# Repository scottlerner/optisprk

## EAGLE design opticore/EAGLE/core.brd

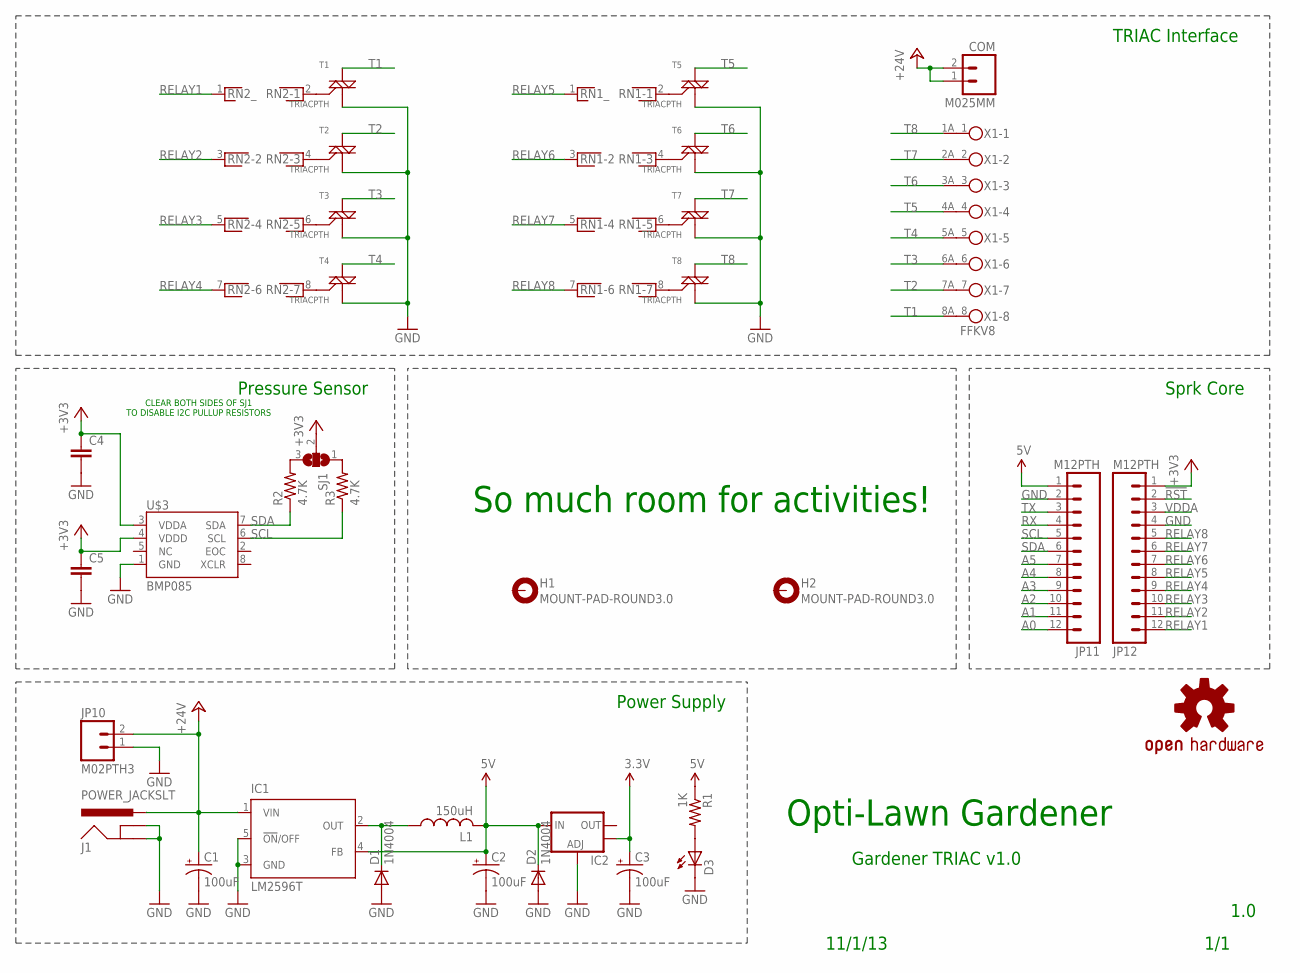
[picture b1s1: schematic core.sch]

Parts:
C1, C2, C3: 100uF; CPOL-RADIAL-100UF-25V; MPN 10NA100MEFC6.3X11
C4, C5: CAP0402-CAP; 0402-CAP
COM: M025MM; SCREWTERMINAL-5MM-2; MPN 724
D1, D2: 1N4004; DO41-10; MPN 1N4004
D3: LED3MM; MPN L-710A8CB/1GD
H1, H2: MOUNT-PAD-ROUND3.0; 3,0-PAD
IC1: LM2596T; T05D; MPN LM2596T-5.0/NOPB
IC2: V_REG_LM1117SOT223; SOT223; MPN LM1117MPX-3.3/NOPB
J1: POWER_JACKSLT; POWER_JACK_SLOT
JP10: M02PTH3; 1X02_LONGPADS
JP11, JP12: M12PTH; 1X12-SMALL-PADS
L1: 150uH; 6000; MPN RLB9012-151KL
LOGO2: OSHW-LOGOL; OSHW-LOGO-L
R1: 1K; AXIAL-0.3; MPN MCF 1W 1K
R2, R3: 4.7K; AXIAL-0.3; MPN MF25 4K7
RN1, RN2: RNX7; RN-8; MPN CSC09A01330RGEK
SJ1: SJ2W; SJ_2
T1, T2, T3, T4, T5, T6, T7, T8: TRIACPTH; TO-92; MPN MAC97A6G
U$3: BMP085
X1: FFKV8

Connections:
3.3V: C3.1 (+), IC2.4 (OUT)
5V: C2.1 (+), D2.C, IC1.4 (FB), IC2.3 (IN), JP11.1, L1.2, R1.P$1 (1)
!RST: JP12.2
+3V3: C4.1, C5.1, JP12.1, SJ1.2, U$3.3 (VDDA), U$3.4 (VDDD)
+24V: C1.1 (+), COM.1, COM.2, IC1.1 (VIN), J1.PWR, JP10.2
A0: JP11.12
A1: JP11.11
A2: JP11.10
A3: JP11.9
A4: JP11.8
A5: JP11.7
GND: C1.2 (-), C2.2 (-), C3.2 (-), C4.2, C5.2, D1.A, D2.A, D3.K (C), IC1.3 (GND), IC1.5 (!ON!/OFF), IC2.1 (ADJ), J1.GND@1 (GNDBREAK), J1.GND@2 (GND), JP10.1, JP11.2, JP12.4, T1.1 (M1), T2.1 (M1), T3.1 (M1), T4.1 (M1), T5.1 (M1), T6.1 (M1), T7.1 (M1), T8.1 (M1), U$3.1 (GND)
unnamed: RN1.4, T6.2 (G)
unnamed: RN1.2, T5.2 (G)
unnamed: RN2.2, T1.2 (G)
unnamed: RN2.4, T2.2 (G)
unnamed: RN2.6, T3.2 (G)
unnamed: RN2.8, T4.2 (G)
unnamed: RN1.6, T7.2 (G)
unnamed: R2.P$2 (2), SJ1.3
unnamed: R3.P$2 (2), SJ1.1
unnamed: D1.C, IC1.2 (OUT), L1.1
unnamed: RN1.8, T8.2 (G)
unnamed: D3.A, R1.P$2 (2)
RELAY1: JP12.12, RN2.1
RELAY2: JP12.11, RN2.3
RELAY3: JP12.10, RN2.5
RELAY4: JP12.9, RN2.7
RELAY5: JP12.8, RN1.1
RELAY6: JP12.7, RN1.3
RELAY7: JP12.6, RN1.5
RELAY8: JP12.5, RN1.7
RX: JP11.4
SCL: JP11.5, R3.P$1 (1), U$3.6 (SCL)
SDA: JP11.6, R2.P$1 (1), U$3.7 (SDA)
T1: T1.3 (M2), X1.8A (2)
T2: T2.3 (M2), X1.7A (2)
T3: T3.3 (M2), X1.6A (2)
T4: T4.3 (M2), X1.5A (2)
T5: T5.3 (M2), X1.4A (2)
T6: T6.3 (M2), X1.3A (2)
T7: T7.3 (M2), X1.2A (2)
T8: T8.3 (M2), X1.1A (2)
TX: JP11.3
VDDA: JP12.3

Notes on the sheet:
TRIAC Interface
Power Supply
Pressure Sensor
CLEAR BOTH SIDES OF SJ1 TO DISABLE I2C PULLUP RESISTORS
Sprk Core
So much room for activities!
Opti-Lawn Gardener
1.0
Gardener TRIAC v1.0
11/1/13
1/1

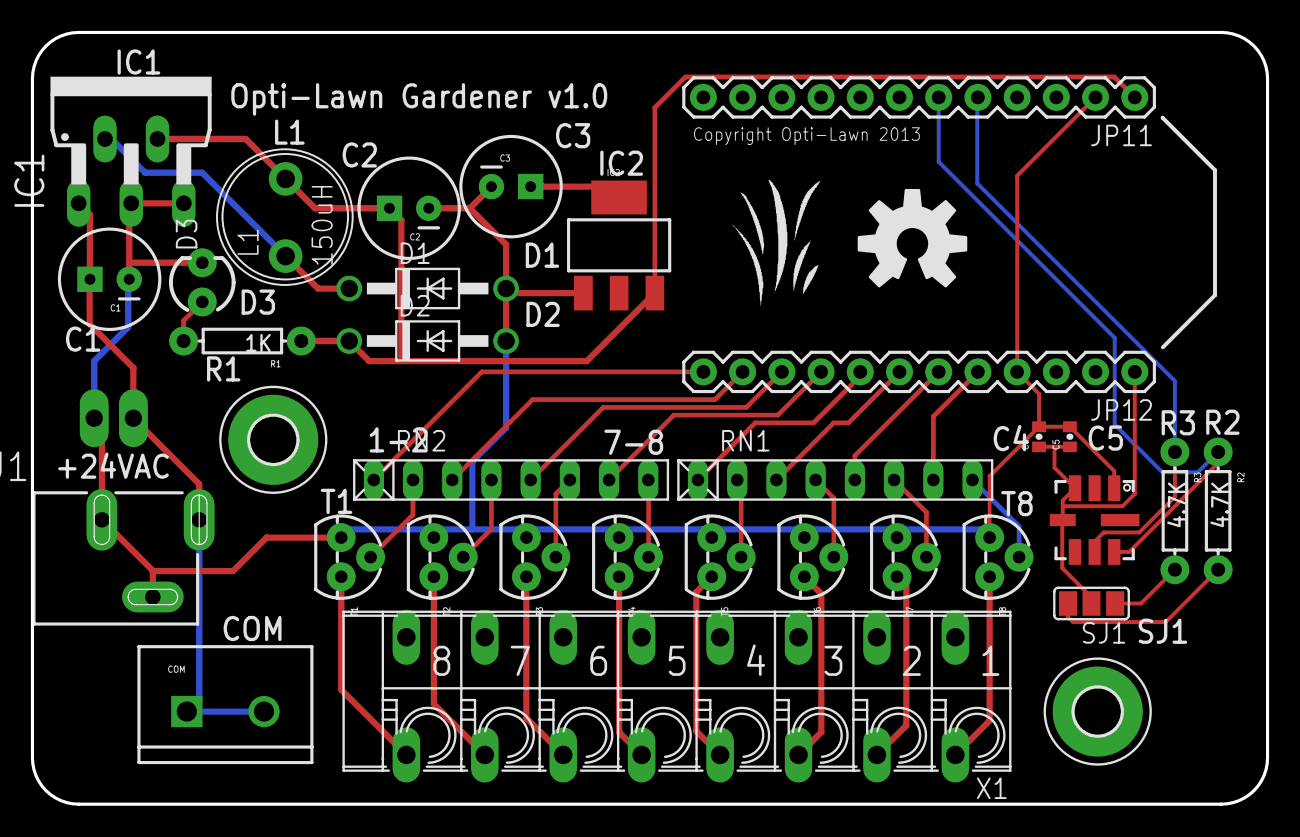
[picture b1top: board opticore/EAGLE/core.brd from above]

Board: 2 copper layers, 80.0 x 50.0 mm, 35 parts (0 on the bottom side), 35 nets.

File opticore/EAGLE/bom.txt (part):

Partlist exported from D:/Users/Scott/Documents/GitHub/optisprk/opticore/EAGLE/core.sch at 11/5/2013 8:52:38 PM

Part  Value              Device             Package               Description                                                                                                                                                                                                        MF MPN              OC_FARNELL OC_NEWARK
C1    100uF              CAP_POLPTH1        CPOL-RADIAL-100UF-25V Capacitor Polarized                                                                                                                                                                                                                                        
C2    100uF              CAP_POLPTH1        CPOL-RADIAL-100UF-25V Capacitor Polarized                                                                                                                                                                                                                                        
C3    100uF              CAP_POLPTH1        CPOL-RADIAL-100UF-25V Capacitor Polarized                                                                                                                                                                                                                                        
C4                       CAP0402-CAP        0402-CAP              Capacitor                                                                                                                                                                                                                                                  
C5                       CAP0402-CAP        0402-CAP              Capacitor                                                                                                                                                                                                                                                  
COM   M025MM             M025MM             SCREWTERMINAL-5MM-2   Standard 2-pin 0.1" header. Use with                                                                                                                                                                                                                       
D1    1N4004             1N4004             DO41-10               DIODE                                                                                                                                                                                                                                                      
D2    1N4004             1N4004             DO41-10               DIODE                                                                                                                                                                                                                                                      
D3                       LED3MM             LED3MM                LEDs                                                                                                                                                                                                                                                       
H1    MOUNT-PAD-ROUND3.0 MOUNT-PAD-ROUND3.0 3,0-PAD               MOUNTING PAD, round                                                                                                                                                                                                                                        
H2    MOUNT-PAD-ROUND3.0 MOUNT-PAD-ROUND3.0 3,0-PAD               MOUNTING PAD, round                                                                                                                                                                                                                                        
IC1   LM2596T            LM2596T            T05D                  SIMPLE SWITCHER® Power Converter 150 kHz 3A Step-Down Voltage Regulator                                                                                                                                               LM2596T-ADJ/LF02 9494162    65K5910  
IC2                      V_REG_LM1117SOT223 SOT223                Voltage Regulator LM1117                                                                                                                                                                                                                                   
J1    POWER_JACKSLT      POWER_JACKSLT      POWER_JACK_SLOT       Power Jack                                                                                                                                                                                                                                                 
JP10  M02PTH3            M02PTH3            1X02_LONGPADS         Standard 2-pin 0.1" header. Use with                                                                                                                                                                                                                       
JP11  M12PTH             M12PTH             1X12-SMALL-PADS       Header 12                                                                                                                                                                                                                                                  
JP12  M12PTH             M12PTH             1X12-SMALL-PADS       Header 12                                                                                                                                                                                                                                                  
L1    150uH              L                  6000                                                                                                                                                                                                                                                                             
LOGO2 OSHW-LOGOL         OSHW-LOGOL         OSHW-LOGO-L           Open Source Hardware Logo This logo indicates the piece of hardware it is found on incorporates a OSHW license and/or adheres to the definition of open source hardware found here: http://freedomdefined.org/OSHW                                         
R1    1K                 RESISTORAXIAL-0.3  AXIAL-0.3             Resistor                                                                                                                                                                                                                                                   
R2    4.7K               RESISTORAXIAL-0.3  AXIAL-0.3             Resistor                                                                                                                                                                                                                                                   
R3    4.7K               RESISTORAXIAL-0.3  AXIAL-0.3             Resistor                                                                                                                                                                                                                                                   
RN1                      RNX7               RN-8                  RESISTOR NETWORK                                                                                                                                                                                                                       unknown    unknown  
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
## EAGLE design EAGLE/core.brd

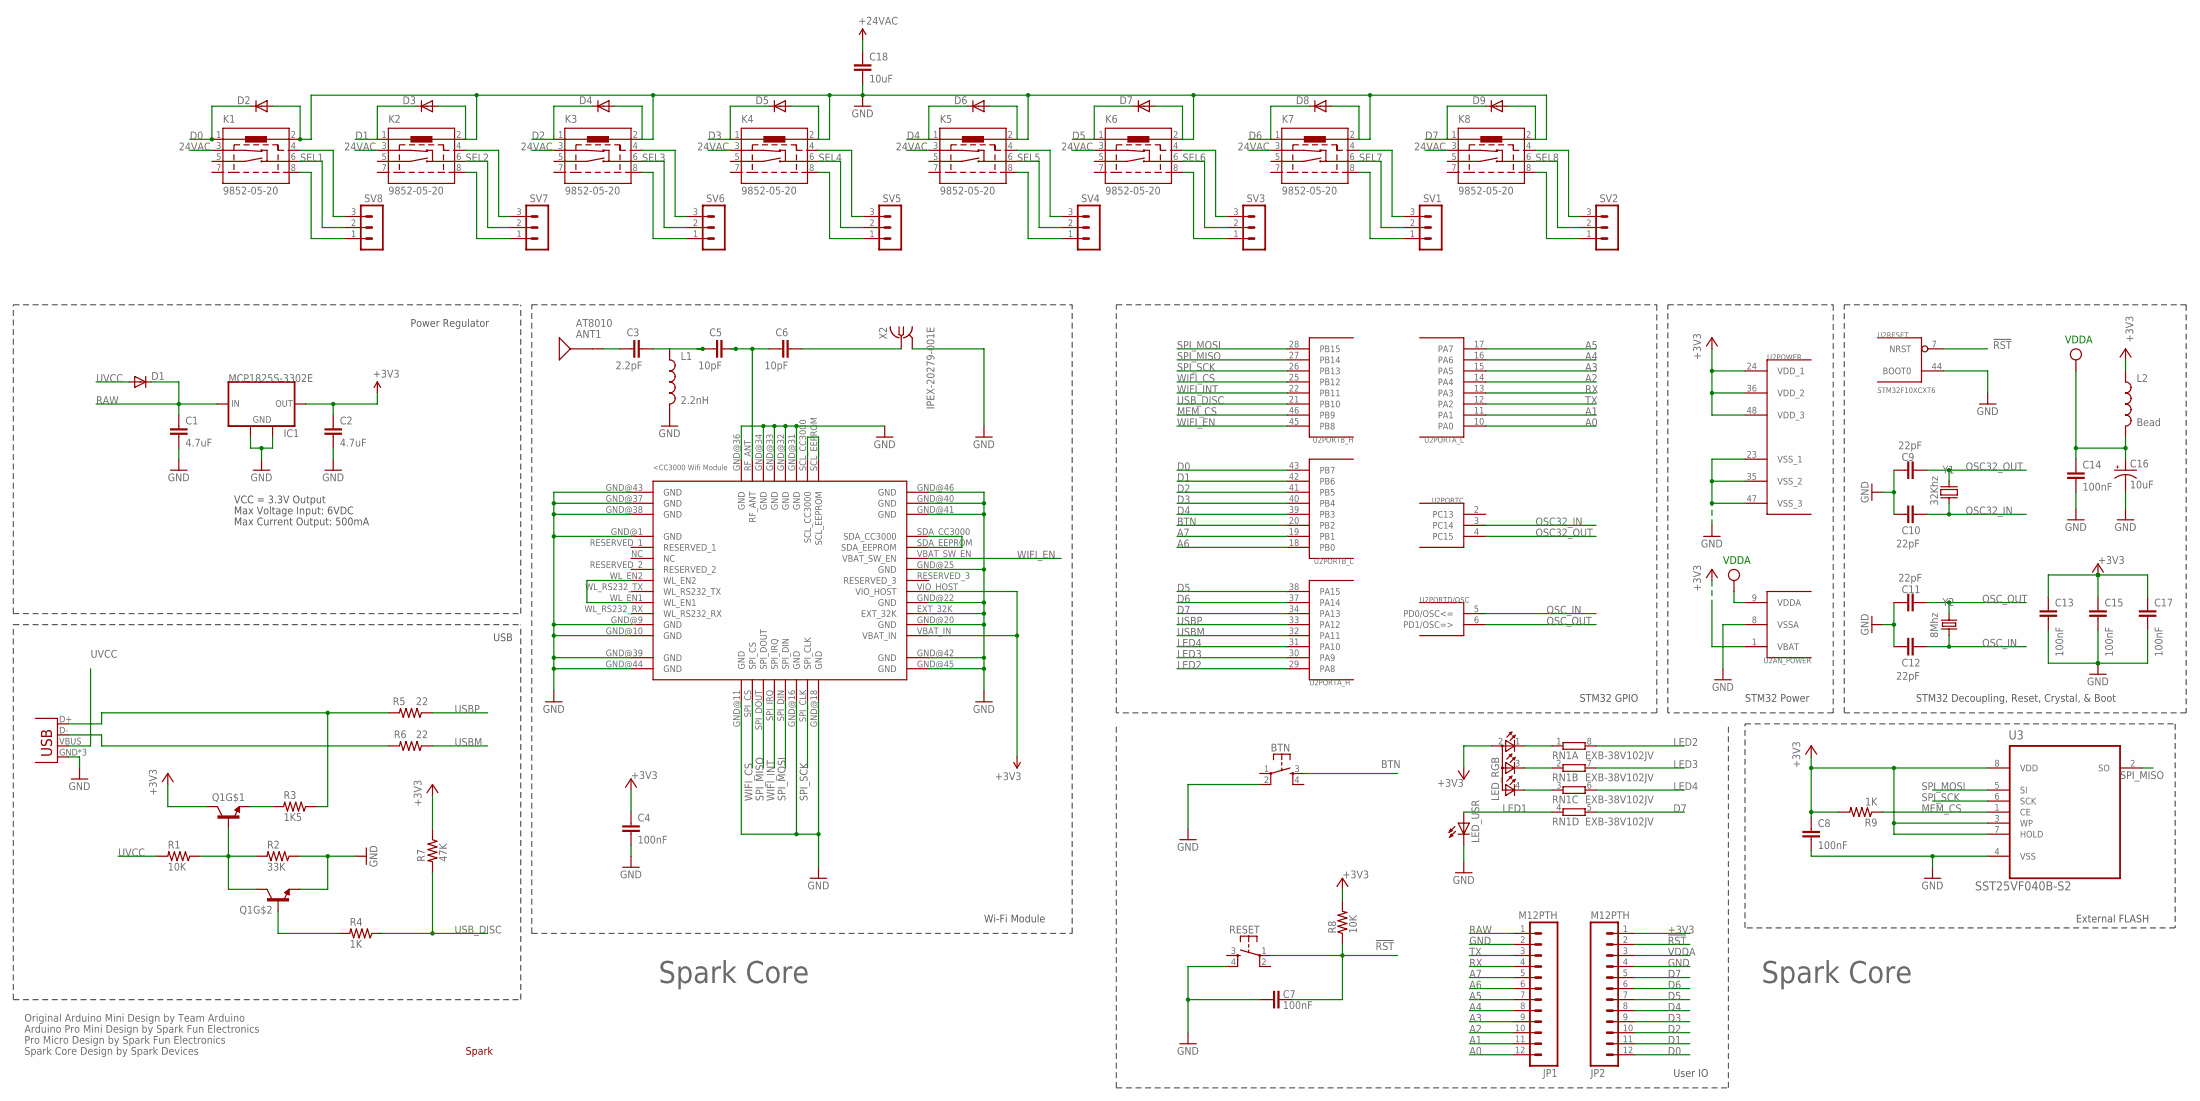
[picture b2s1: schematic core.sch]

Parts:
ANT1: AT8010
BTN: KMR211GLFS; TACTILE_SWITCH_SMD
C1, C2: 4.7uF; C0603
C3: 2.2pF; C0603
C4, C7, C8, C13, C14, C15, C17: 100nF; C0603
C5, C6: 10pF; C0603
C9, C10, C11, C12: 22pF; C0603
C16: 10uF; EIA3216
C18: 10uF; C0603
D1, D2, D3, D4, D5, D6, D7, D8, D9: DIODESOD; SOD-323
IC1: MCP1825S-3302E; SOT223
JP1, JP2: M12PTH; 1X12-SMALL-PADS
K1, K2, K3, K4, K5, K6, K7, K8: 9852-05-20; 9852-20
L1: 2.2nH; 0603
L2: Bead; 0603
LED_RGB: TOPLED-3PLCC; P-LCC-4-3
LED_USR: LED0603; LED-0603
Q1: MMDT3904; SOT363
R1, R8: 10K; R0603
R2: 33K; R0603
R3: 1K5; R0603
R4, R9: 1K; R0603
R5, R6: 22; R0603
R7: 47K; R0603
RESET: KMR211GLFS; TACTILE_SWITCH_SMD
RN1: EXB-38V102JV; EXB38V
SV1, SV2, SV3, SV4, SV5, SV6, SV7, SV8: MA03-1
U1: CC3000
U2: STM32F10XCXT6; TQFP48
U3: SST25VF040B-S2; SOIC127P790X216-8N
U$1: SPARK_LOGO2
X1: USB-MICROB; USB-MICROB-SLOT-HOLE
X2: IPEX-20279-001E
Y1: 32Khz; FC135
Y2: 8Mhz; CRYSTAL-SMD-5X3

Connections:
24VAC: C18.1, K1.3, K2.3, K3.3, K4.3, K5.3, K6.3, K7.3, K8.3
!RST: C7.2, JP2.2, R8.1, RESET.1, U2.7 (NRST)
+3V3: C2.1, C4.1, C8.1, C13.1, C15.1, C17.1, IC1.3 (OUT), JP2.1, L2.1, LED_RGB.2 (A2), Q1.3 (C), R7.1, R8.2, R9.2, U1.VBAT_IN, U1.VIO_HOST, U2.1 (VBAT), U2.24 (VDD_1), U2.36 (VDD_2), U2.48 (VDD_3), U3.3 (WP), U3.7 (HOLD), U3.8 (VDD)
A0: JP1.12, U2.10 (PA0)
A1: JP1.11, U2.11 (PA1)
A2: JP1.10, U2.14 (PA4)
A3: JP1.9, U2.15 (PA5)
A4: JP1.8, U2.16 (PA6)
A5: JP1.7, U2.17 (PA7)
A6: JP1.6, U2.18 (PB0)
A7: JP1.5, U2.19 (PB1)
BTN: BTN.3, U2.20 (PB2)
D0: D2.1 (C), JP2.12, K1.1, U2.43 (PB7)
D1: JP2.11, K2.1, U2.42 (PB6)
D2: JP2.10, K3.1, U2.41 (PB5)
D3: JP2.9, K4.1, U2.40 (PB4)
D4: JP2.8, K5.1, U2.39 (PB3)
D5: JP2.7, K6.1, U2.38 (PA15)
D6: JP2.6, K7.1, U2.37 (PA14)
D7: JP2.5, K8.1, RN1.5 (2), U2.34 (PA13)
D8: D3.1 (C)
D9: D4.1 (C)
D10: D5.1 (C)
D11: D6.1 (C)
D12: D7.1 (C)
D13: D8.1 (C)
D14: D9.1 (C)
GND: BTN.2, C1.2, C2.2, C4.2, C7.1, C8.2, C9.2, C10.2, C11.2, C12.2, C13.2, C14.2, C15.2, C16.C (-), C17.2, C18.2, D2.2 (A), IC1.2 (GND), IC1.4 (GND), JP1.2, JP2.4, K1.2, K2.2, K3.2, K4.2, K5.2, K6.2, K7.2, K8.2, L1.2, LED_USR.C, Q1.1 (E), R2.1, RESET.4, U1.EXT_32K, U1.GND@1 (GND), U1.GND@9 (GND), U1.GND@10 (GND), U1.GND@11 (GND), U1.GND@16 (GND), U1.GND@18 (GND), U1.GND@20 (GND), U1.GND@22 (GND), U1.GND@25 (GND), U1.GND@31 (GND), U1.GND@32 (GND), U1.GND@33 (GND), U1.GND@34 (GND), U1.GND@36 (GND), U1.GND@37 (GND), U1.GND@38 (GND), U1.GND@39 (GND), U1.GND@40 (GND), U1.GND@41 (GND), U1.GND@42 (GND), U1.GND@43 (GND), U1.GND@44 (GND), U1.GND@45 (GND), U1.GND@46 (GND), U2.8 (VSSA), U2.23 (VSS_1), U2.35 (VSS_2), U2.44 (BOOT0), U2.47 (VSS_3), U3.4 (VSS), X1.GND, X1.MT1 (GND), X1.MT2 (GND), X2.2@1 (GND), X2.2@2 (GND)
GND1: D3.2 (A)
GND2: D4.2 (A)
GND3: D5.2 (A)
GND4: D6.2 (A)
GND5: D7.2 (A)
GND6: D8.2 (A)
GND7: D9.2 (A)
LED1: LED_USR.A, RN1.4 (1)
LED2: RN1.8 (2), U2.29 (PA8)
LED3: RN1.7 (2), U2.30 (PA9)
LED4: RN1.6 (2), U2.31 (PA10)
MEM_CS: R9.1, U2.46 (PB9), U3.1 (CE)
unnamed: R3.1, R5.2, X1.D+
unnamed: C6.2, X2.1
unnamed: ANT1.SIG, C3.1
unnamed: C5.2, C6.1, U1.RF_ANT
unnamed: C3.2, C5.1, L1.1
unnamed: R6.2, X1.D-
unnamed: U1.SCL_CC3000, U1.SCL_EEPROM
unnamed: Q1.2 (B), R4.2
unnamed: U1.WL_EN1, U1.WL_EN2
unnamed: LED_RGB.1 (CRED), RN1.1
unnamed: LED_RGB.3 (CBLUE), RN1.2 (1)
unnamed: Q1.5 (B), Q1.6 (C), R1.1, R2.2
unnamed: LED_RGB.4 (CGREEN), RN1.3 (1)
unnamed: U1.SDA_CC3000, U1.SDA_EEPROM
unnamed: Q1.4 (E), R3.2
unnamed: K8.8, SV2.1
unnamed: K8.4, SV2.3
unnamed: K7.8, SV1.1
unnamed: K7.4, SV1.3
unnamed: K6.8, SV3.1
unnamed: K6.4, SV3.3
unnamed: K5.8, SV4.1
unnamed: K5.4, SV4.3
unnamed: K4.8, SV5.1
unnamed: K4.4, SV5.3
unnamed: K3.8, SV6.1
unnamed: K3.4, SV6.3
unnamed: K2.8, SV7.1
unnamed: K2.4, SV7.3
unnamed: K1.8, SV8.1
unnamed: K1.4, SV8.3
OSC32_IN: C10.1, U2.3 (PC14), Y1.X1 (1)
OSC32_OUT: C9.1, U2.4 (PC15), Y1.X2 (2)
OSC_IN: C12.1, U2.5 (PD0/OSC<=), Y2.1
OSC_OUT: C11.1, U2.6 (PD1/OSC=>), Y2.3 (2)
RAW: C1.1, D1.1 (C), IC1.1 (IN), JP1.1
RX: JP1.4, U2.13 (PA3)
SEL1: K1.6, SV8.2
SEL2: K2.6, SV7.2
SEL3: K3.6, SV6.2
SEL4: K4.6, SV5.2
SEL5: K5.6, SV4.2
SEL6: K6.6, SV3.2
SEL7: K7.6, SV1.2
SEL8: K8.6, SV2.2
SPI_MISO: U1.SPI_DOUT, U2.27 (PB14), U3.2 (SO)
SPI_MOSI: U1.SPI_DIN, U2.28 (PB15), U3.5 (SI)
SPI_SCK: U1.SPI_CLK, U2.26 (PB13), U3.6 (SCK)
TX: JP1.3, U2.12 (PA2)
USBM: R6.1, U2.32 (PA11)
USBP: R5.1, U2.33 (PA12)
USB_DISC: R4.1, R7.2, U2.21 (PB10)
UVCC: D1.2 (A), R1.2, X1.VBUS
VDDA: C14.1, C16.A (+), JP2.3, L2.2, U2.9 (VDDA)
WIFI_CS: U1.SPI_CS, U2.25 (PB12)
WIFI_EN: U1.VBAT_SW_EN, U2.45 (PB8)
WIFI_INT: U1.SPI_IRQ, U2.22 (PB11)

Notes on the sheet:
Original Arduino Mini Design by Team Arduino
Arduino Pro Mini Design by Spark Fun Electronics
Max Voltage Input: 6VDC
Max Current Output: 500mA
Power Regulator
VCC = 3.3V Output
Pro Micro Design by Spark Fun Electronics
Spark Core Design by Spark Devices
STM32 Decoupling, Reset, Crystal, & Boot
STM32 GPIO
STM32 Power
External FLASH
User IO
USB
Spark Core
Wi-Fi Module
VDDA

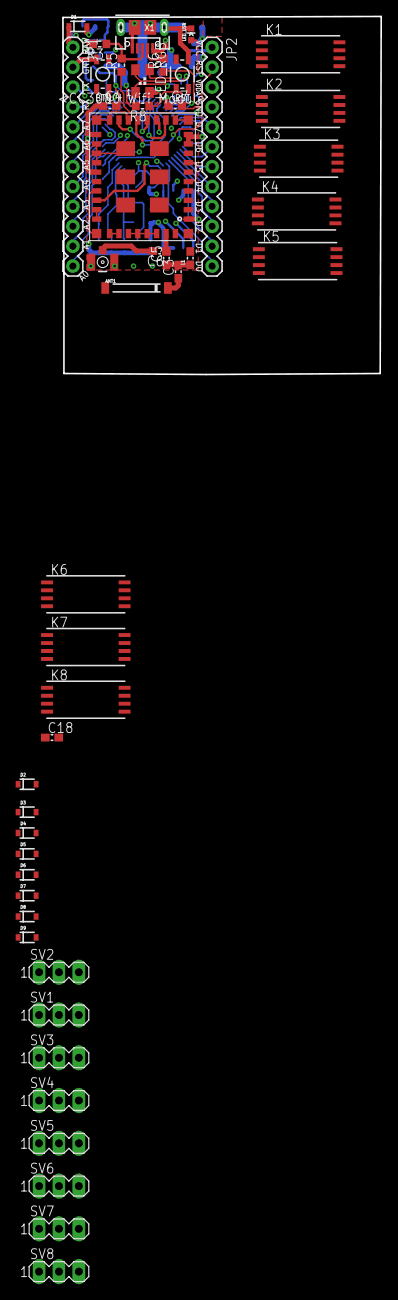
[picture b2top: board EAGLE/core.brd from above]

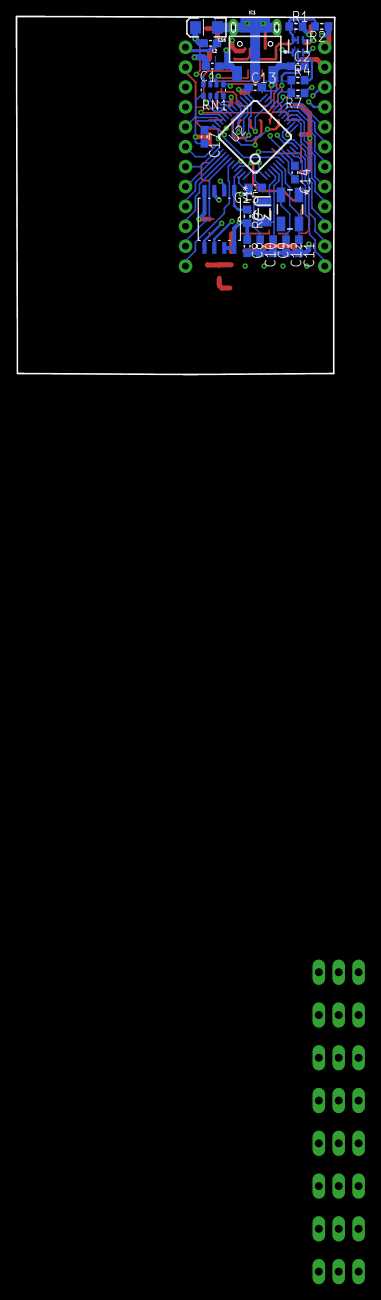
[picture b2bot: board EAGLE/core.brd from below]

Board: 4 copper layers, 40.6 x 45.7 mm, 72 parts (25 on the bottom side), 83 nets.

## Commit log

2013-08-21 Initial Commit to GitHub
    6546546
2013-08-21 Uploading EAGLE files
    This git project will probably be overwritten.
2013-08-21 Revert "Initial Commit to GitHub"
    This reverts commit 9c8e7e8ea3b3e0f55e0435f3f81987d36a1364e5.
2013-08-21 Why can't I commit these?!
    Daaaahhh!!!
2013-08-21 First real commit
    Please let this work.
2013-08-21 Initial placement of relays
    Still need to do a lot of work. Placement is temporary.
    LEDs and the rest of the components need to be placed.
    One problem is that I can't move what they originally did. Option #1: Redo what they did. (not happening) Option #2: Try adding their schematic as a part then placing it on a new shm. Option #3: Try 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
2013-08-22 Finished Initial Placement
    I still need to route everything, but I think it's a pretty
    space-efficient design as is. Probably needs to be organized a little
    better.
    NOTE: With the free version of EAGLE, I cannot make a board bigger than
    100mm x 80mm. In those dimensions, I cannot place all relays in a
    straight line. Hence the inverted 'L' shape.
2013-09-01 Close to final revision
    I'm working on laying down the final placement as well as the ground
    planes. I'll try and work on it soon.
2013-09-04 Partially done with routing
    Mainly working on layout now. Adding a custom image to see how it looks.
    Also, I think I'm going to replace the capacitors for the pressure
    sensor.
2013-09-04 Adding custom images
    Pushing to get on windows.
2013-09-04 Under Pressure
    Adding a bit of personality to the board. Essentially have a good
    layout. Still need to do the changes from 2 commits ago.
2013-09-10 Stuff I did on the plane to PHL
    Most just moving some stuff around and laying down traces.
2013-09-11 More routing
    Slowly getting closer to 'optimal', but that pressure sensor is
    annoying.
2013-09-16 Initial Final Draft
    At this point, I have done a decent amount of routing, re-routing, and replacement. I am fairly confident that everything will work. I would still want to do another run through for bug fixes though.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
2013-09-20 Major fix with relays
    The previous version would break everything.
2013-09-25 Rewiring some things
    Still haven't implemented 24V power supply.
2013-09-25 Redoing power supply section
    This isn't done yet. I still have to connect the 24VAC to the solenoids.
    All GND pins on solenoids are tied together then to COMMON.
2013-10-11 Not sure
    I haven't worked on this for a while. I assume it is trying to fix the
    power problem. Still need to figure that out.
2013-10-25 Upgrading to power supply that will work
    Proven method from previous designs.
2013-10-27 Placed and Routed new 24VAC to 5VDC
    Hopefully this works as expected. Horray for Rev 1!
2013-10-27 Accidentally Missed these commits.
    Don't know exactly what they are.
2013-10-28 Added TRIACS instead of Relays
    In theory this will work more efficiently. Hopefully it does.
2013-10-28 Trying to get to a finished v1.0
    Added silkscreen and tried to generate Gerber files. Committing for other computer.
2013-10-29 Final stages of V1.0
    Need to do final ERC and style checks then it's off to the board house.
2013-11-02 Sending my baby off to the board house!
    Version 1.0 of the board is done and is being prepped for the board house. Just trying to decide on who to print with...
2013-11-02 Official Final v1.0 commit
    Includes gerber files to send to board house.
2013-11-07 Adding BOM
    Idk what the board updates are.

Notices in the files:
opticore/EAGLE/core.brd:
Copyright Opti-Lawn 2013
parts and their libraries:
SparkFun-Passives: Licensing: CC v3.0 Share-Alike You are welcome to use this library for commercial purposes.
